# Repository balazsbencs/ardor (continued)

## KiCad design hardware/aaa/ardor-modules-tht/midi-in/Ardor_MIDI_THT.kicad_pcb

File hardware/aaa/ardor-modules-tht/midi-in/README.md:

# Isolated MIDI input / 3.3 V UART / HAND ASSEMBLY

T1 hand-assembly PCB: 85 × 70 mm. **Unbuilt engineering prototype.**

[KiCad project](Ardor_MIDI_THT.kicad_pro) · [Manual BOM](BOM.csv) · [Schematic](review/schematic.pdf) · [Bare-board Gerbers](assembly/Ardor_MIDI_THT-Gerbers.zip)

Use a female five-pin DIN panel socket. Wire numbered DIN contact 4 to J202.1 and contact 5 to J202.2. Leave DIN 1/2/3 and shell unwired; insulate the socket shell. Bond the enclosure to J203.1. Do not treat MIDI contact 5 as ground. Fit the exact H11L1M optocoupler; other optocouplers have different switching thresholds or pinouts.

Supply 5 V / 10 mA and 3.3 V / 5 mA. Set the host UART to 31250 baud, 8-N-1. J101.4 is a 3.3 V output into the host RX input.

Commission: inspect DIP orientation and D201 band, verify 5 V at U201.6 and 3.3 V at the output pull-up, then verify idle UART HIGH. Send known MIDI notes and check UART timing and decoding. Test long cables and real transmitters because the axial protection parts have different capacitance/RF behavior. Functional ground-loop isolation is not safety isolation.

## Connector pin assignments

Directions are relative to this board. Standard header square pads identify pin 1. Read reference and pin numbers from the back silkscreen; mirrored CAD exports are labelled as back views.

### J202 — MIDI INPUT FROM DIN SOCKET

| Pin | Net | Direction | Connect to |
|---|---|---|---|
| 1 | MIDI_4 | MIDI INPUT | Female DIN socket numbered contact 4. |
| 2 | MIDI_5 | MIDI INPUT | Female DIN socket numbered contact 5. |

### J101 — POWER INPUT + UART OUTPUT TO HOST

| Pin | Net | Direction | Connect to |
|---|---|---|---|
| 1 | +5V | POWER INPUT | Positive output of the matching regulated supply. |
| 2 | +3V3 | POWER INPUT | Positive output of the matching regulated supply. |
| 3 | GND | GROUND | Host or cable ground / 0 V. |
| 4 | MIDI_RX | OUTPUT | Host UART RX input, 31250 baud, 8-N-1. Do not connect to host TX. |

### J203 — METAL CASE BOND + GROUND

| Pin | Net | Direction | Connect to |
|---|---|---|---|
| 1 | CHASSIS | BOND | Aluminium enclosure bonding point; insulate the MIDI DIN shell. |
| 2 | GND | GROUND | Host or cable ground / 0 V. |

## Assembly and files

Fit low-profile axial parts first, then sockets/headers and radial capacitors. Match diode bands, electrolytic polarity and IC notches to the PCB. Install the ICs or ADC breakout last. H1/H2 are 2.2 mm nonplated M2 mounting holes, not electrical terminals. Check enclosure clearance and capacitor/socket height: these boards are larger than M1.

Use the manual BOM and the bare-board Gerber/drill ZIP. There is no SMT assembly order. Front silkscreen shows component references; the front fabrication drawing shows package outlines and orientation; use the BOM for values. Back silk includes port functions and pin numbers. Native checks and package manifests are under `verification/`; they do not replace prototype measurements.

[Assembly accessories](assembly/accessories.csv) list sockets, shunts and panel items in addition to the PCB component BOM.

[Family guide](../README.md) · [Substitution sources](../SOURCES.md) · [Native validation](verification/validation.json)

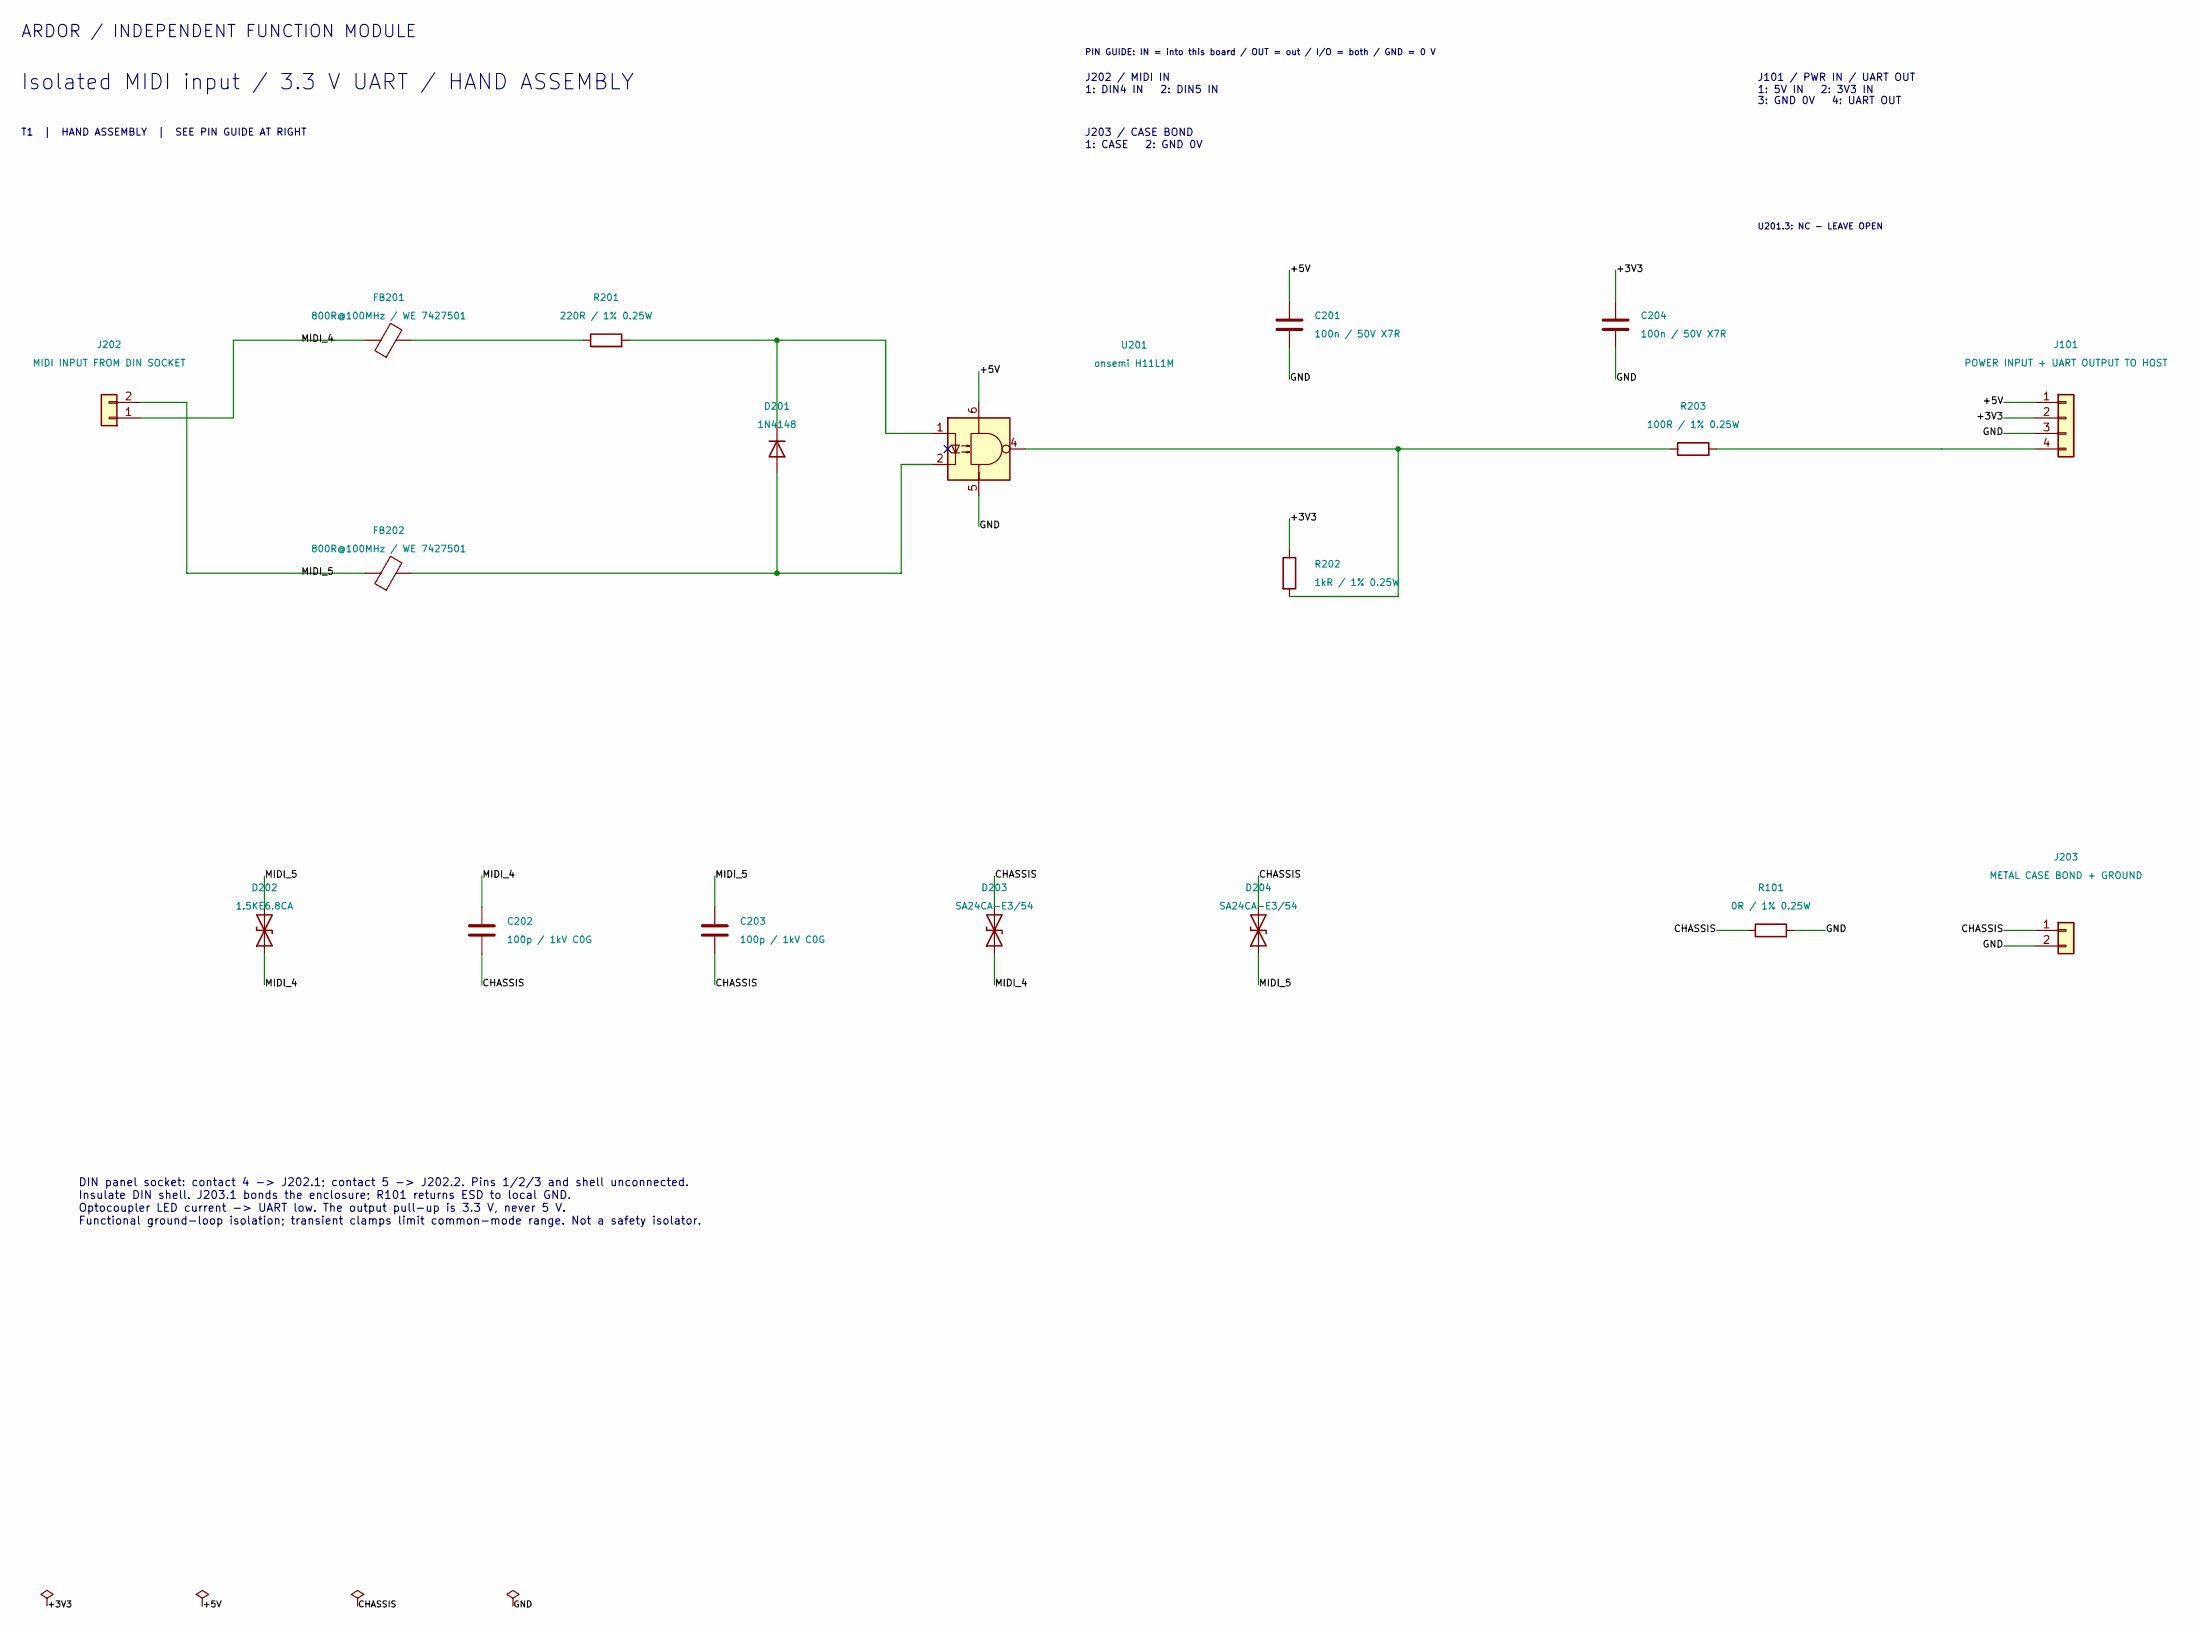
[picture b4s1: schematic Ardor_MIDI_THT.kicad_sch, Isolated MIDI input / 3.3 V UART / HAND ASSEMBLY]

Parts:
C201, C204: 100n / 50V X7R; C_Disc_D5.0mm_W2.5mm_P5.00mm; MPN 100nF 50V X7R radial, 5mm lead pitch
C202, C203: 100p / 1kV C0G; C_Disc_D5.0mm_W2.5mm_P5.00mm; MPN 100pF 1kV C0G disc, 5mm lead pitch
D201: 1N4148; D_DO-35_SOD27_P7.62mm_Horizontal; MPN Vishay 1N4148-TAP
D202: 1.5KE6.8CA; D_TVS_DC_1.5KE_P15.24mm; MPN DC Components 1.5KE6.8CA (HESTORE 100.4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
D203, D204: SA24CA-E3/54; D_DO-15_P10.16mm_Horizontal; MPN Vishay SA24CA-E3/54
FB201, FB202: 800R@100MHz / WE 7427501; Ferrite_WE_7427501_P15.24mm; MPN Wurth Elektronik 7427501
J101: POWER INPUT + UART OUTPUT TO HOST; PinHeader_1x04_P2.54mm_Vertical; MPN PinHeader_1x04_P2.54mm_Vertical
J202: MIDI INPUT FROM DIN SOCKET; PinHeader_1x02_P2.54mm_Vertical; MPN PinHeader_1x02_P2.54mm_Vertical
J203: METAL CASE BOND + GROUND; PinHeader_1x02_P2.54mm_Vertical; MPN PinHeader_1x02_P2.54mm_Vertical
R101: 0R / 1% 0.25W; R_Axial_DIN0207_L6.3mm_D2.5mm_P10.16mm_Horizontal; MPN Axial metal film 0Ω 1% 0.25W
R201: 220R / 1% 0.25W; R_Axial_DIN0207_L6.3mm_D2.5mm_P10.16mm_Horizontal; MPN Axial metal film 220Ω 1% 0.25W
R202: 1kR / 1% 0.25W; R_Axial_DIN0207_L6.3mm_D2.5mm_P10.16mm_Horizontal; MPN Axial metal film 1kΩ 1% 0.25W
R203: 100R / 1% 0.25W; R_Axial_DIN0207_L6.3mm_D2.5mm_P10.16mm_Horizontal; MPN Axial metal film 100Ω 1% 0.25W
U201: onsemi H11L1M; DIP-6_W7.62mm; MPN onsemi H11L1M

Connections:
/+3V3: C204.1, J101.2, R202.1
/+5V: C201.1, J101.1, U201.6
/CHASSIS: C202.2, C203.2, D203.2 (A2), D204.2 (A2), J203.1, R101.1
/GND: C201.2, C204.2, J101.3, J203.2, R101.2, U201.5
/MIDI_4: C202.1, D202.1 (A1), D203.1 (A1), FB201.1, J202.1
/MIDI_5: C203.1, D202.2 (A2), D204.1 (A1), FB202.1, J202.2
unnamed: D201.2 (A), FB202.2, U201.2
unnamed: D201.1 (K), R201.2, U201.1
unnamed: FB201.2, R201.1
unnamed: J101.4, R203.2
unnamed: R202.2, R203.1, U201.4

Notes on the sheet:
ARDOR / INDEPENDENT FUNCTION MODULE
Isolated MIDI input / 3.3 V UART / HAND ASSEMBLY
T1 | HAND ASSEMBLY | SEE PIN GUIDE AT RIGHT
DIN panel socket: contact 4 -> J202.1; contact 5 -> J202.2. Pins 1/2/3 and shell unconnected. Insulate DIN shell. J203.1 bonds the enclosure; R101 returns ESD to local GND. Optocoupler LED current -> UART low. The output pull-up is 3.3 V, never 5 V. Functional ground-loop isolation; transient clamp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
PIN GUIDE: IN = into this board / OUT = out / I/O = both / GND = 0 V
J202 / MIDI IN
1: DIN4 IN 2: DIN5 IN
J101 / PWR IN / UART OUT
1: 5V IN 2: 3V3 IN
3: GND 0V 4: UART OUT
J203 / CASE BOND
1: CASE 2: GND 0V
U201.3: NC - LEAVE OPEN

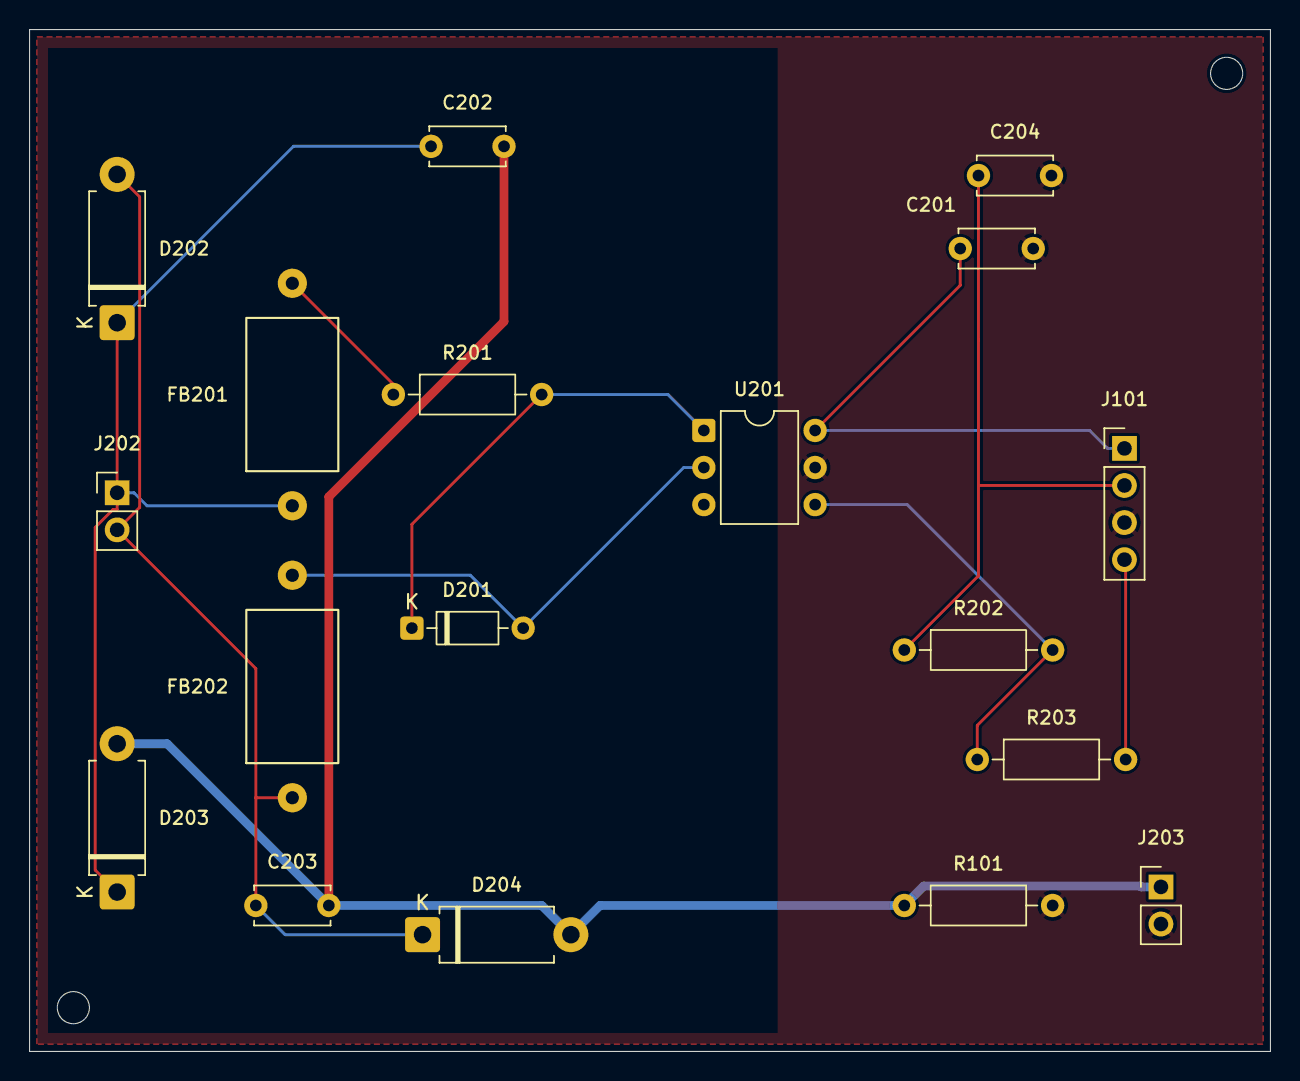
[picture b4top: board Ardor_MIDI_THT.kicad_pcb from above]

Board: 2 copper layers, 85.0 x 70.0 mm, 20 parts (0 on the bottom side), 11 nets.

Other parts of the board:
H1, H2: MountingHole_2.2mm_M2

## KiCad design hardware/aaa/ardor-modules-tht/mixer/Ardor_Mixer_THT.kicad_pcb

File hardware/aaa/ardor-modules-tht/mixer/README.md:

# Stereo buffer / mono average / AC outputs / HAND ASSEMBLY

T1 hand-assembly PCB: 100 × 75 mm. **Unbuilt engineering prototype.**

[KiCad project](Ardor_Mixer_THT.kicad_pro) · [Manual BOM](BOM.csv) · [Schematic](review/schematic.pdf) · [Bare-board Gerbers](assembly/Ardor_Mixer_THT-Gerbers.zip)

Supply 5 V / 10 mA. Fit **MCP6022-I/P** DIP-8 amplifiers; TLV9002 SOIC parts from M1 do not fit. Use bipolar 10 µF coupling capacitors C401/C402/C407/C408/C409. C101 and C403 are ordinary polarized radial capacitors, positive on pad 1.

Inputs are line-level, no greater than 1 Vrms per channel. Outputs drive loads of at least 10 kΩ. OUT_MONO is `(LEFT + RIGHT) / 2`; all three outputs are AC-coupled. Feeding only one channel gives half its amplitude at the mono output. Feed both channels for a full-level mono source. The board is not an instrument preamp or headphone amplifier.

Commission with no signal: check the filtered 5 V rail and about 2.5 V at VREF and the internal buffer outputs. Check near-zero settled DC on the external outputs. Feed separate 1 kHz left/right tones and verify unity stereo buffers, mono averaging and channel separation. Check clipping, noise and oscillation across the audio band. Keep external harnesses short; exposed audio sockets need entry protection.

## Connector pin assignments

Directions are relative to this board. Standard header square pads identify pin 1. Read reference and pin numbers from the back silkscreen; mirrored CAD exports are labelled as back views.

### J101 — 5V POWER INPUT

| Pin | Net | Direction | Connect to |
|---|---|---|---|
| 1 | +5V | POWER INPUT | Positive output of the matching regulated supply. |
| 2 | GND | GROUND | Host or cable ground / 0 V. |

### J102 — STEREO AUDIO INPUT FROM SOURCE

| Pin | Net | Direction | Connect to |
|---|---|---|---|
| 1 | AUDIO_L | INPUT | DAC/codec left audio output, <=1 Vrms. |
| 2 | GND | GROUND | Host or cable ground / 0 V. |
| 3 | AUDIO_R | INPUT | DAC/codec right audio output, <=1 Vrms. |

### J103 — BUFFERED STEREO + MONO AUDIO OUTPUT

| Pin | Net | Direction | Connect to |
|---|---|---|---|
| 1 | OUT_L | OUTPUT | Left line input of another device, >=10k load. |
| 2 | GND | GROUND | Host or cable ground / 0 V. |
| 3 | OUT_R | OUTPUT | Right line input of another device, >=10k load. |
| 4 | OUT_MONO | OUTPUT | Mono line input, >=10k load. Signal is (L+R)/2. |

## Assembly and files

Fit low-profile axial parts first, then sockets/headers and radial capacitors. Match diode bands, electrolytic polarity and IC notches to the PCB. Install the ICs or ADC breakout last. H1/H2 are 2.2 mm nonplated M2 mounting holes, not electrical terminals. Check enclosure clearance and capacitor/socket height: these boards are larger than M1.

Use the manual BOM and the bare-board Gerber/drill ZIP. There is no SMT assembly order. Front silkscreen shows component references; the front fabrication drawing shows package outlines and orientation; use the BOM for values. Back silk includes port functions and pin numbers. Native checks and package manifests are under `verification/`; they do not replace prototype measurements.

[Assembly accessories](assembly/accessories.csv) list sockets, shunts and panel items in addition to the PCB component BOM.

[Family guide](../README.md) · [Substitution sources](../SOURCES.md) · [Native validation](verification/validation.json)

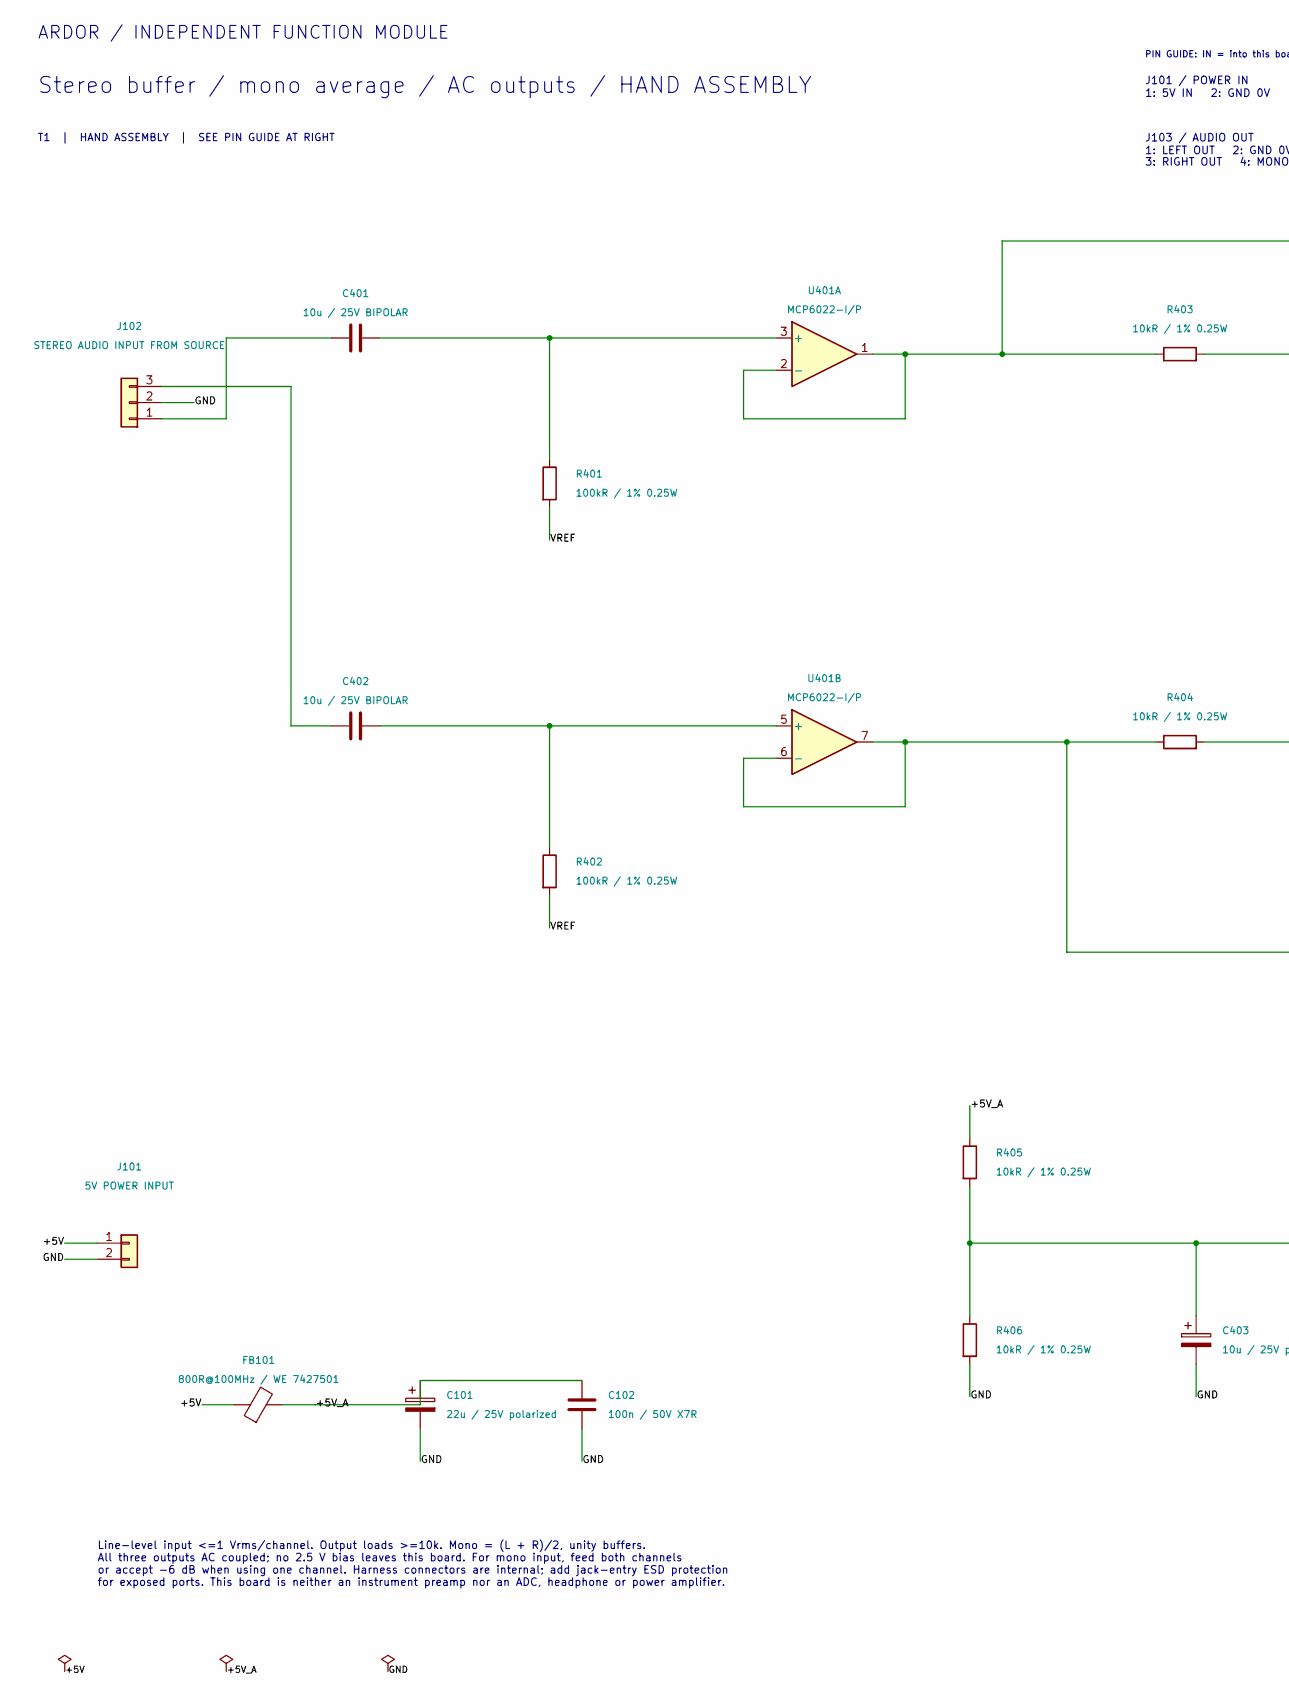
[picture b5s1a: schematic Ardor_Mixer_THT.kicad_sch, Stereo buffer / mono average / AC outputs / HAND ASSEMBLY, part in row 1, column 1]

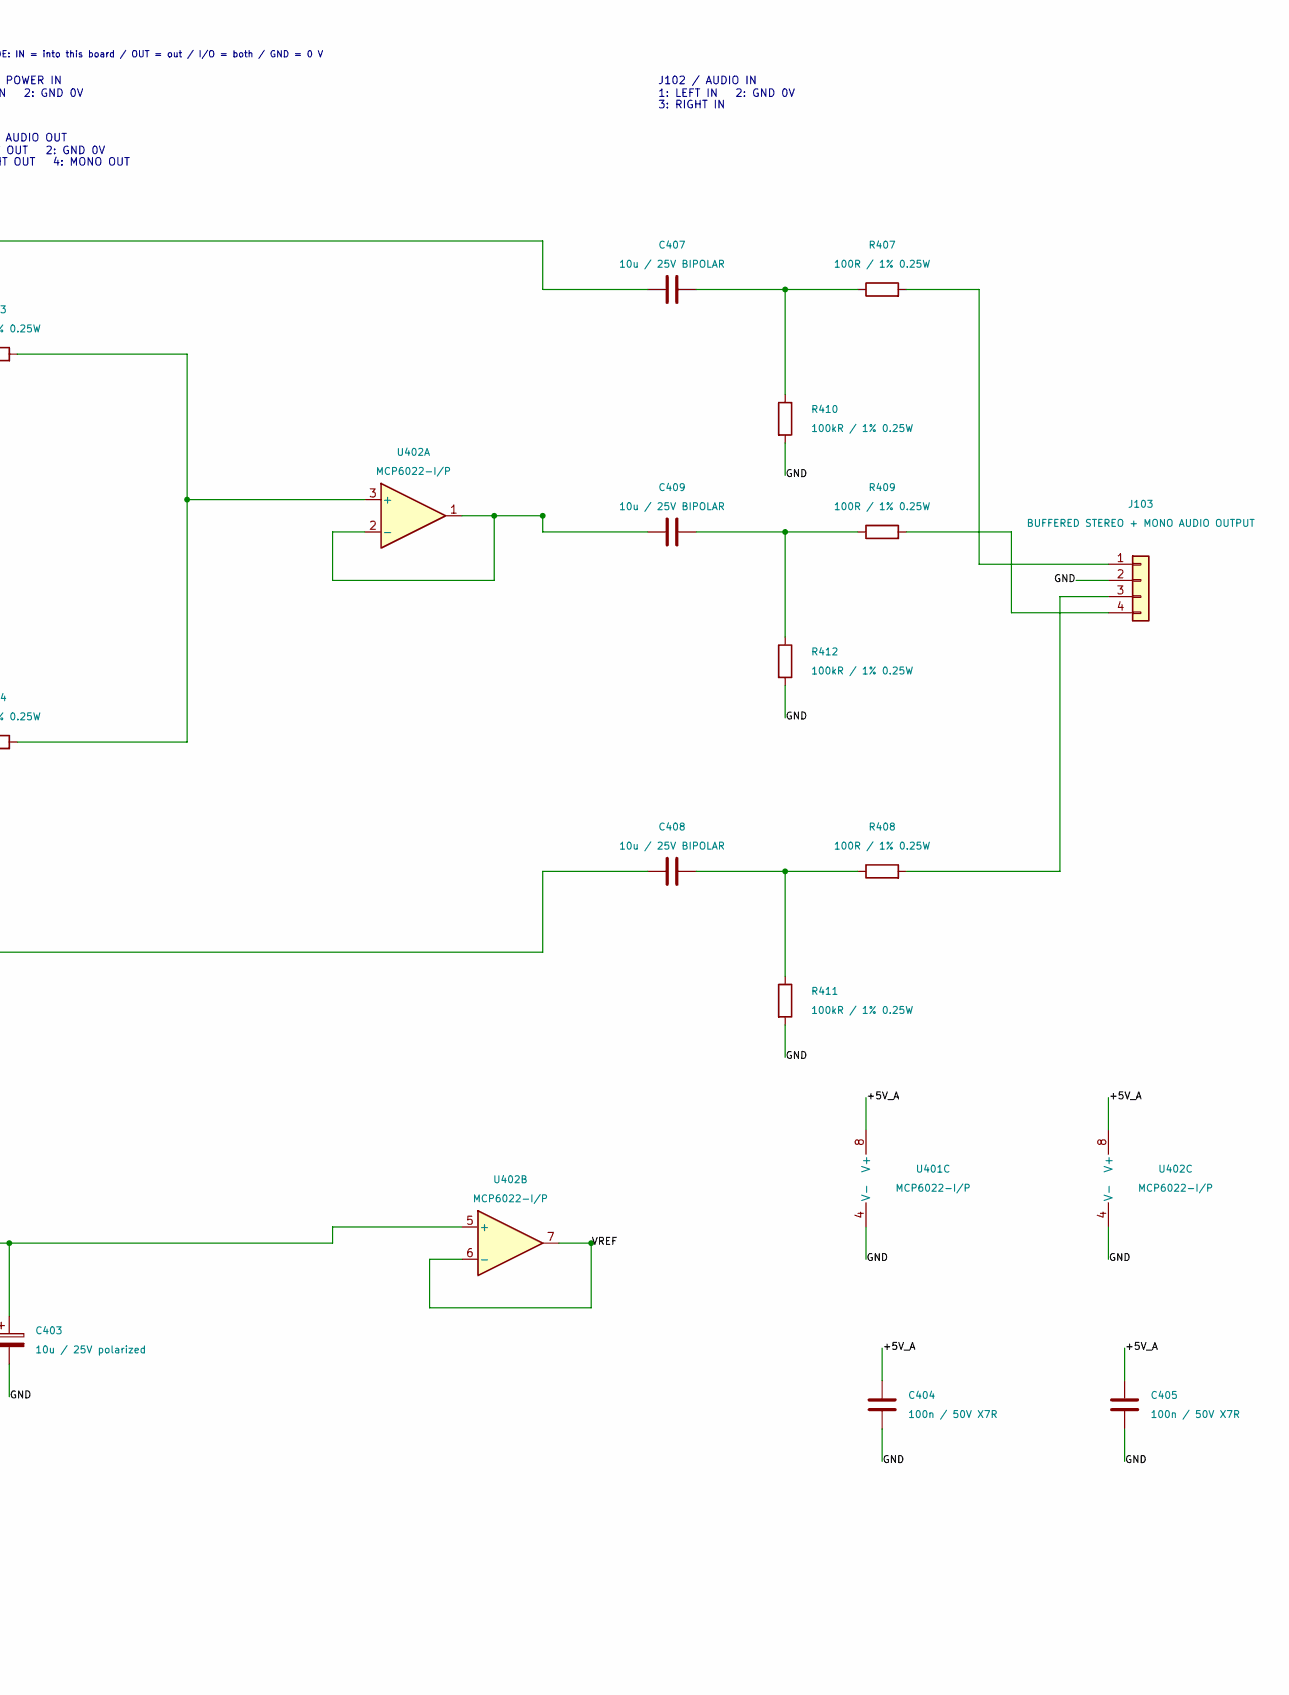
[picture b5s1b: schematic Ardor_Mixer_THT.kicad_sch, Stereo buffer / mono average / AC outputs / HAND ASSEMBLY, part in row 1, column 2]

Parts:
C101: 22u / 25V polarized; CP_Radial_D6.3mm_P2.50mm; MPN Radial electrolytic 22uF 25V, D<=6.3mm 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
C102, C404, C405: 100n / 50V X7R; C_Disc_D5.0mm_W2.5mm_P5.00mm; MPN 100nF 50V X7R radial, 5mm lead pitch
C401, C402, C407, C408, C409: 10u / 25V BIPOLAR; CP_Bipolar_D6.3mm_P2.50mm; MPN Nichicon UES1E100MDM
C403: 10u / 25V polarized; CP_Radial_D6.3mm_P2.50mm; MPN Radial electrolytic 10uF 25V, D<=6.3mm 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
FB101: 800R@100MHz / WE 7427501; Ferrite_WE_7427501_P15.24mm; MPN Wurth Elektronik 7427501
J101: 5V POWER INPUT; PinHeader_1x02_P2.54mm_Vertical; MPN PinHeader_1x02_P2.54mm_Vertical
J102: STEREO AUDIO INPUT FROM SOURCE; PinHeader_1x03_P2.54mm_Vertical; MPN PinHeader_1x03_P2.54mm_Vertical
J103: BUFFERED STEREO + MONO AUDIO OUTPUT; PinHeader_1x04_P2.54mm_Vertical; MPN PinHeader_1x04_P2.54mm_Vertical
R401, R402, R410, R411, R412: 100kR / 1% 0.25W; R_Axial_DIN0207_L6.3mm_D2.5mm_P10.16mm_Horizontal; MPN Axial metal film 100kΩ 1% 0.25W
R403, R404, R405, R406: 10kR / 1% 0.25W; R_Axial_DIN0207_L6.3mm_D2.5mm_P10.16mm_Horizontal; MPN Axial metal film 10kΩ 1% 0.25W
R407, R408, R409: 100R / 1% 0.25W; R_Axial_DIN0207_L6.3mm_D2.5mm_P10.16mm_Horizontal; MPN Axial metal film 100Ω 1% 0.25W
U401, U402: MCP6022-I/P; DIP-8_W7.62mm_Socket; MPN Microchip MCP6022-I/P

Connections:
/+5V: FB101.1, J101.1
/+5V_A: C101.1, C102.1, C404.1, C405.1, FB101.2, R405.1, U401.8 (V+), U402.8 (V+)
/GND: C101.2, C102.2, C403.2, C404.2, C405.2, J101.2, J102.2, J103.2, R406.2, R410.2, R411.2, R412.2, U401.4 (V-), U402.4 (V-)
/VREF: R401.2, R402.2, U402.6 (-), U402.7
unnamed: C407.2, R407.1, R410.1
unnamed: C408.2, R408.1, R411.1
unnamed: C409.2, R409.1, R412.1
unnamed: C401.1, J102.1
unnamed: C402.1, J102.3
unnamed: J103.1, R407.2
unnamed: J103.3, R408.2
unnamed: J103.4, R409.2
unnamed: C401.2, R401.1, U401.3 (+)
unnamed: C407.1, R403.1, U401.1, U401.2 (-)
unnamed: C402.2, R402.1, U401.5 (+)
unnamed: C408.1, R404.1, U401.6 (-), U401.7
unnamed: R403.2, R404.2, U402.3 (+)
unnamed: C409.1, U402.1, U402.2 (-)
unnamed: C403.1, R405.2, R406.1, U402.5 (+)

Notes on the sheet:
ARDOR / INDEPENDENT FUNCTION MODULE
Stereo buffer / mono average / AC outputs / HAND ASSEMBLY
T1 | HAND ASSEMBLY | SEE PIN GUIDE AT RIGHT
Line-level input <=1 Vrms/channel. Output loads >=10k. Mono = (L + R)/2, unity buffers. All three outputs AC coupled; no 2.5 V bias leaves this board. For mono input, feed both channels or accept -6 dB when using one channel. Harness connectors are internal; add jack-entry ESD protection for expose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
PIN GUIDE: IN = into this board / OUT = out / I/O = both / GND = 0 V
J101 / POWER IN
1: 5V IN 2: GND 0V
J102 / AUDIO IN
1: LEFT IN 2: GND 0V
3: RIGHT IN
J103 / AUDIO OUT
1: LEFT OUT 2: GND 0V
3: RIGHT OUT 4: MONO OUT

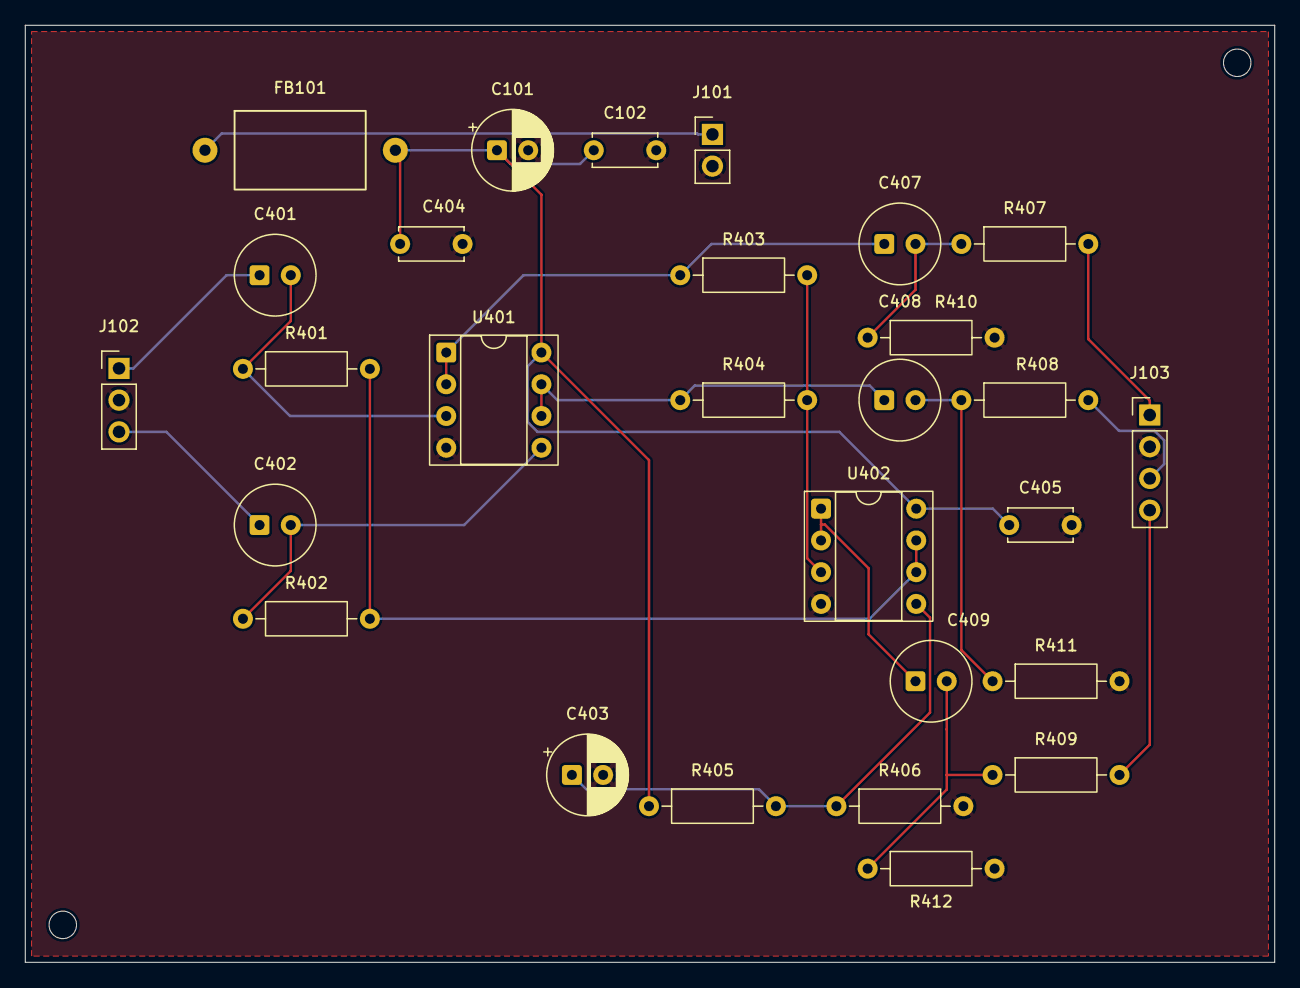
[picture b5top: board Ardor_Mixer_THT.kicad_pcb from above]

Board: 2 copper layers, 100.0 x 75.0 mm, 30 parts (0 on the bottom side), 19 nets.

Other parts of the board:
H1, H2: MountingHole_2.2mm_M2

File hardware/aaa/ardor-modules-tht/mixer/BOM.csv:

Reference,Value,Footprint,Purchasing specification,Assembly
J102,STEREO AUDIO INPUT FROM SOURCE,Connector_PinHeader_2.54mm:PinHeader_1x03_P2.54mm_Vertical,PinHeader_1x03_P2.54mm_Vertical,THT manual
J101,5V POWER INPUT,Connector_PinHeader_2.54mm:PinHeader_1x02_P2.54mm_Vertical,PinHeader_1x02_P2.54mm_Vertical,THT manual
J103,"BUFFERED STEREO + MONO AUDIO
OUTPUT",Connector_PinHeader_2.54mm:PinHeader_1x04_P2.54mm_Vertical,PinHeader_1x04_P2.54mm_Vertical,THT manual
FB101,800R@100MHz / WE 7427501,Ardor_THT:Ferrite_WE_7427501_P15.24mm,Wurth Elektronik 7427501,THT manual
C101,22u / 25V polarized,Capacitor_THT:CP_Radial_D6.3mm_P2.50mm,"Radial electrolytic 22uF 25V, D<=6.3mm P2.5mm",THT manual
C102,100n / 50V X7R,Capacitor_THT:C_Disc_D5.0mm_W2.5mm_P5.00mm,"100nF 50V X7R radial, 5mm lead pitch",THT manual
C401,10u / 25V BIPOLAR,Ardor_THT:CP_Bipolar_D6.3mm_P2.50mm,Nichicon UES1E100MDM,THT manual
R401,100kR / 1% 0.25W,Resistor_THT:R_Axial_DIN0207_L6.3mm_D2.5mm_P10.16mm_Horizontal,Axial metal film 100kΩ 1% 0.25W,THT manual
U401,MCP6022-I/P,Package_DIP:DIP-8_W7.62mm_Socket,Microchip MCP6022-I/P,THT manual
R403,10kR / 1% 0.25W,Resistor_THT:R_Axial_DIN0207_L6.3mm_D2.5mm_P10.16mm_Horizontal,Axial metal film 10kΩ 1% 0.25W,THT manual
C402,10u / 25V BIPOLAR,Ardor_THT:CP_Bipolar_D6.3mm_P2.50mm,Nichicon UES1E100MDM,THT manual
R402,100kR / 1% 0.25W,Resistor_THT:R_Axial_DIN0207_L6.3mm_D2.5mm_P10.16mm_Horizontal,Axial metal film 100kΩ 1% 0.25W,THT manual
R404,10kR / 1% 0.25W,Resistor_THT:R_Axial_DIN0207_L6.3mm_D2.5mm_P10.16mm_Horizontal,Axial metal film 10kΩ 1% 0.25W,THT manual
U402,MCP6022-I/P,Package_DIP:DIP-8_W7.62mm_Socket,Microchip MCP6022-I/P,THT manual
C407,10u / 25V BIPOLAR,Ardor_THT:CP_Bipolar_D6.3mm_P2.50mm,Nichicon UES1E100MDM,THT manual
R407,100R / 1% 0.25W,Resistor_THT:R_Axial_DIN0207_L6.3mm_D2.5mm_P10.16mm_Horizontal,Axial metal film 100Ω 1% 0.25W,THT manual
R410,100kR / 1% 0.25W,Resistor_THT:R_Axial_DIN0207_L6.3mm_D2.5mm_P10.16mm_Horizontal,Axial metal film 100kΩ 1% 0.25W,THT manual
C408,10u / 25V BIPOLAR,Ardor_THT:CP_Bipolar_D6.3mm_P2.50mm,Nichicon UES1E100MDM,THT manual
R408,100R / 1% 0.25W,Resistor_THT:R_Axial_DIN0207_L6.3mm_D2.5mm_P10.16mm_Horizontal,Axial metal film 100Ω 1% 0.25W,THT manual
R411,100kR / 1% 0.25W,Resistor_THT:R_Axial_DIN0207_L6.3mm_D2.5mm_P10.16mm_Horizontal,Axial metal film 100kΩ 1% 0.25W,THT manual
C409,10u / 25V BIPOLAR,Ardor_THT:CP_Bipolar_D6.3mm_P2.50mm,Nichicon UES1E100MDM,THT manual
R409,100R / 1% 0.25W,Resistor_THT:R_Axial_DIN0207_L6.3mm_D2.5mm_P10.16mm_Horizontal,Axial metal film 100Ω 1% 0.25W,THT manual
R412,100kR / 1% 0.25W,Resistor_THT:R_Axial_DIN0207_L6.3mm_D2.5mm_P10.16mm_Horizontal,Axial metal film 100kΩ 1% 0.25W,THT manual
R405,10kR / 1% 0.25W,Resistor_THT:R_Axial_DIN0207_L6.3mm_D2.5mm_P10.16mm_Horizontal,Axial metal film 10kΩ 1% 0.25W,THT manual
R406,10kR / 1% 0.25W,Resistor_THT:R_Axial_DIN0207_L6.3mm_D2.5mm_P10.16mm_Horizontal,Axial metal film 10kΩ 1% 0.25W,THT manual
C403,10u / 25V polarized,Capacitor_THT:CP_Radial_D6.3mm_P2.50mm,"Radial electrolytic 10uF 25V, D<=6.3mm P2.5mm",THT manual
C404,100n / 50V X7R,Capacitor_THT:C_Disc_D5.0mm_W2.5mm_P5.00mm,"100nF 50V X7R radial, 5mm lead pitch",THT manual
C405,100n / 50V X7R,Capacitor_THT:C_Disc_D5.0mm_W2.5mm_P5.00mm,"100nF 50V X7R radial, 5mm lead pitch",THT manual
